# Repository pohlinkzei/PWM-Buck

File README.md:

# PWM-Buck
AVR-based control unit for car heating and ventilation in combination with an auxiliary heating

Its based on a Atmega88/168/328 AVR with a buck-converter power amplifier. It is made to driva a 
200W Motor for car heating and to display the water temperature, the temperature of the power 
transistors and the battery voltage. 

Here is where the development begun:
http://www.t4forum.de/wbb3/board19-technik-bereich/board120-umbauten-tuning/board8-tipps-und-tricks/165848-gemeinschaftsentwicklung-t4forums-pwm-modul/

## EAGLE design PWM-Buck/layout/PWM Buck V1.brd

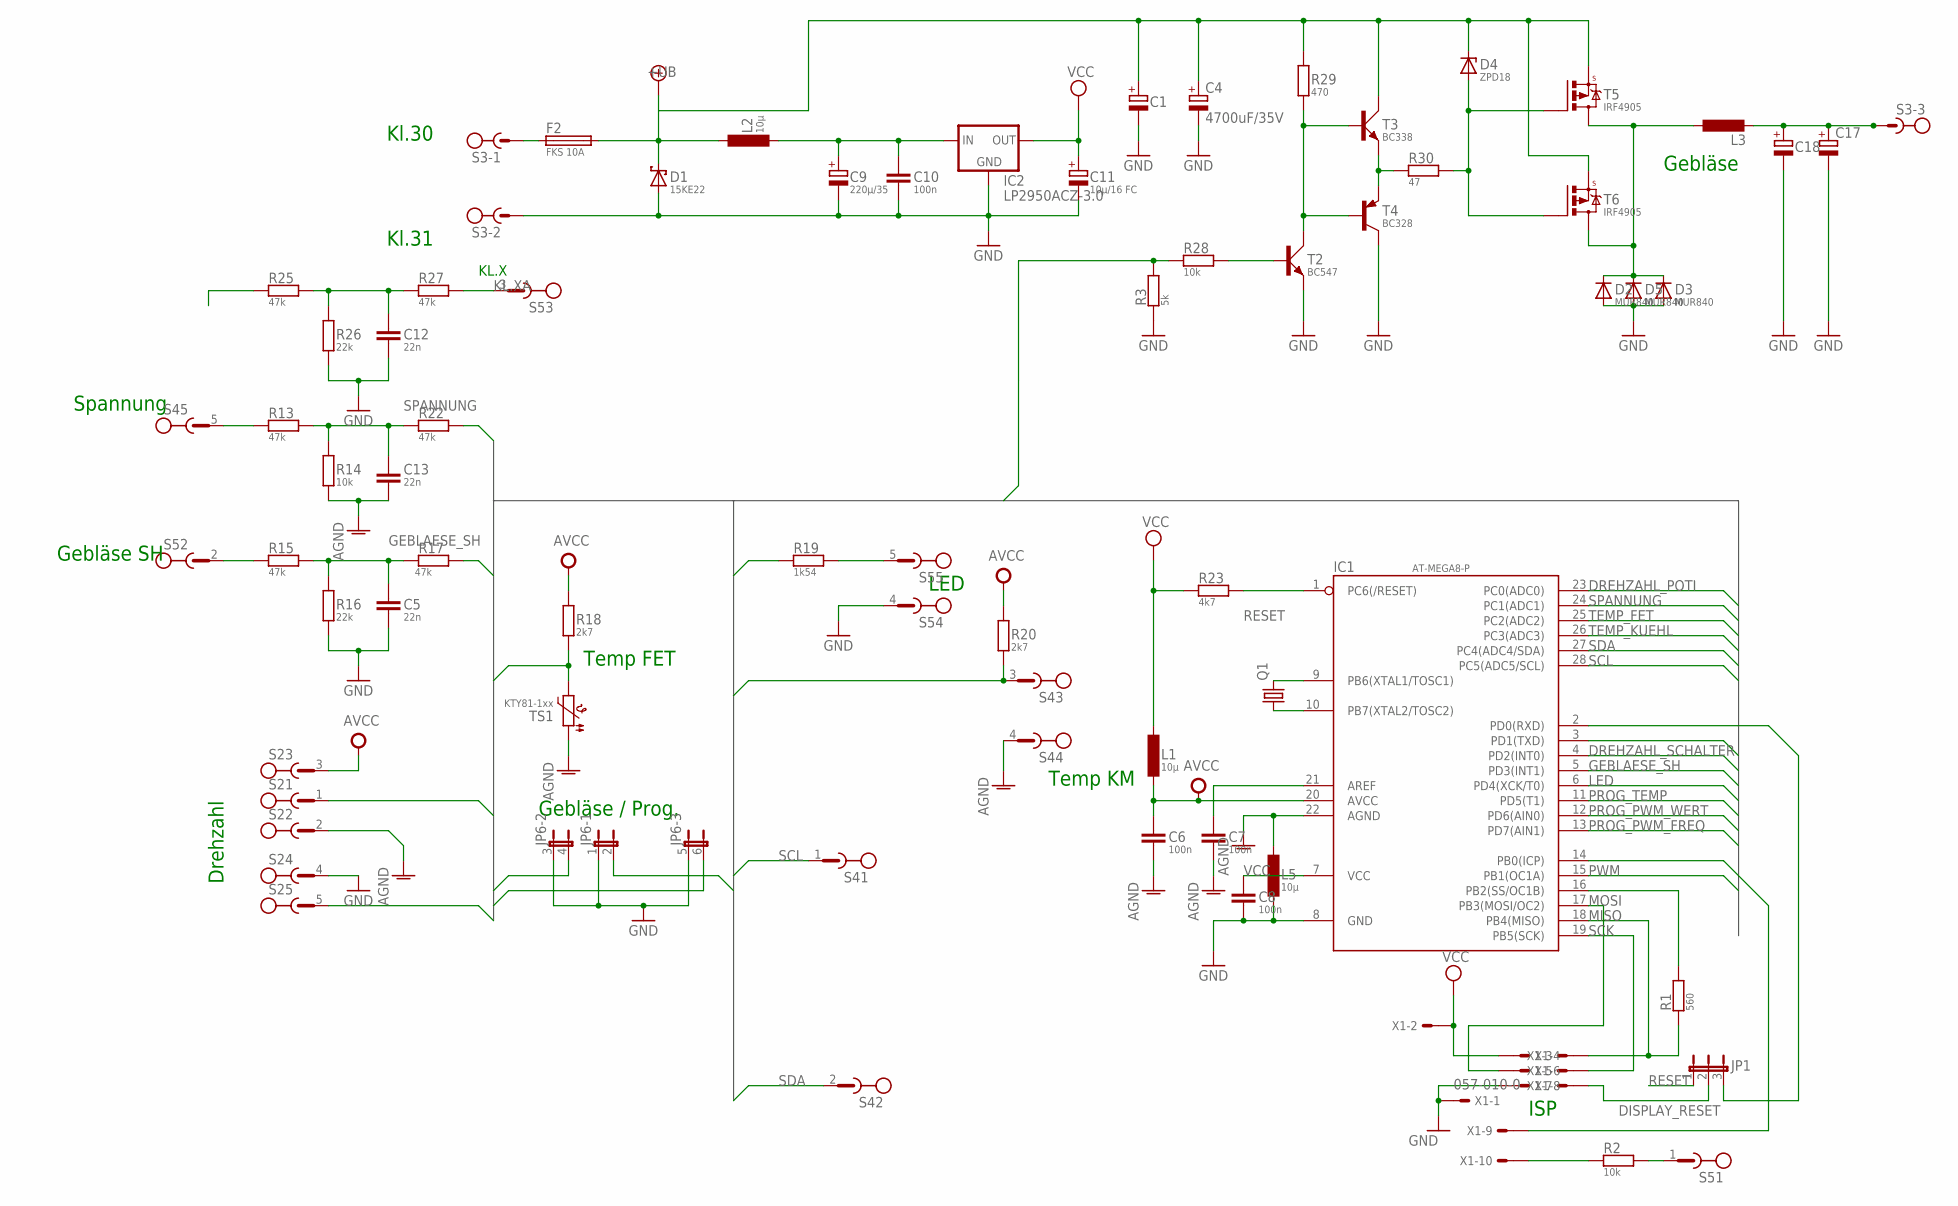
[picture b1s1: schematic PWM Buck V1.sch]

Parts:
C1, C18: C_POL_5-10.5; E5-10.5
C4: 4700uF/35V; E7,5-18
C5, C12, C13: 22n; C_75_SCHMAL
C6, C7, C8: 100n; C_50_SCHMAL
C9: 220µ/35; E5-10.5
C10: 100n; C_75_SCHMAL
C11: 10µ/16 FC; E2.5-5
C17: CPOL-EUE5-13; E5-13
D1: 15KE22; DO201T15
D2, D3, D5: MUR840; TO220ACS
D4: ZPD18; DO35Z10
F2: FKS 10A; FKS
IC1: AT-MEGA8-P; AT-MEGA8P
IC2: LP2950ACZ-3.0; TO92
JP1: JP2E; JP2
JP6: JP3QE; JP3Q
L1, L2, L5: 10µ; L-2200-12,7
L3: L-EU0207/12; 0207/12
Q1: CRYSTALTC26V; TC26V
R1: 560; R_10
R2, R14, R28: 10k; R_10
R3: 5k; R_10
R13, R15, R17, R22, R25, R27: 47k; R_10
R16, R26: 22k; R_10
R18: 2k7; R_10
R19: 1k54; R_10
R20: 2k7; R_12
R23: 4k7; R_10
R29: 470; R_10
R30: 47; R_10
S2: CON-PLATINE_5-POLIG
S3: CON-RIA-220-03; RIA-220-03
S4, S5: CON-RIA-183-05; RIA-183-05
T2: BC547; SOT54A-WIDE
T3: BC338; SOT54A-WIDE
T4: BC328; TO92_WIDE
T5, T6: IRF4905; TO220BV
TS1: KTY81-1xx; SOD70
X1: 057-010-0

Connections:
+UB: C1.+, C4.+, D1.C, D4.C, F2.2, L2.2, R29.2, T3.C, T5.S, T6.S
AGND: C6.2, C7.2, C13.1, IC1.22 (AGND), L5.2, R14.1, S2.2, S4.4, TS1.1
AVCC: C6.1, IC1.20 (AVCC), L1.1, R18.2, R20.2, S2.3
BEL_K58B: R2.2, X1.10
BEL_SH: IC1.14 (PB0(ICP)), X1.9
DISPLAY_RESET: JP1.2, X1.7
DREHZAHL_POTI: IC1.23 (PC0(ADC0)), S2.1
DREHZAHL_SCHALTER: IC1.4 (PD2(INT0)), S2.5
GATE: D4.A, R30.1, T5.G, T6.G
GEBLAESE_OUT: D2.C, D3.C, D5.C, L3.1, T5.D, T6.D
GEBLAESE_SH: IC1.5 (PD3(INT1)), R17.1
GND: C1.-, C4.-, C5.1, C8.2, C9.-, C10.2, C11.-, C12.1, C17.-, C18.-, D1.A, D2.A, D3.A, D5.A, IC1.8 (GND), IC2.2 (GND), JP6.1, JP6.3 (1), JP6.5 (1), L5.1, R3.2, R16.1, R26.1, S2.4, S3.2, S5.4, T2.E, T4.3 (C), X1.1, X1.8
KL.X: IC1.3 (PD1(TXD)), R25.1
KL.XA: R27.1, S5.3
LED: IC1.6 (PD4(XCK/T0)), R19.2
MISO: IC1.18 (PB4(MISO)), R1.1, X1.3
MOSI: IC1.17 (PB3(MOSI/OC2)), X1.6
unnamed: IC1.9 (PB6(XTAL1/TOSC1)), Q1.2
unnamed: IC1.10 (PB7(XTAL2/TOSC2)), Q1.1
unnamed: IC1.16 (PB2(SS/OC1B)), R1.2
unnamed: F2.1, S3.1
unnamed: IC1.2 (PD0(RXD)), JP1.3
unnamed: C5.2, R15.2, R16.2, R17.2
unnamed: C9.+, C10.1, IC2.3 (IN), L2.1
unnamed: R29.1, T2.C, T3.B, T4.2 (B)
unnamed: R2.1, S5.1
unnamed: C17.+, C18.+, L3.2, S3.3
unnamed: C7.1, IC1.21 (AREF)
unnamed: R28.1, T2.B
unnamed: R30.2, T3.E, T4.1 (E)
unnamed: C12.2, R25.2, R26.2, R27.2
unnamed: R19.1, S5.5
NIX: C13.2, R13.2, R14.2, R22.1
PROG_PWM_FREQ: IC1.13 (PD7(AIN1)), JP6.6 (2)
PROG_PWM_WERT: IC1.12 (PD6(AIN0)), JP6.4 (2)
PROG_TEMP: IC1.11 (PD5(T1)), JP6.2
PWM: IC1.15 (PB1(OC1A)), R3.1, R28.2
RESET: IC1.1 (PC6(/RESET)), JP1.1, R23.2
SCK: IC1.19 (PB5(SCK)), X1.5
SCL: IC1.28 (PC5(ADC5/SCL)), S4.1
SDA: IC1.27 (PC4(ADC4/SDA)), S4.2
SH: R15.1, S5.2
SPANNUNG: IC1.24 (PC1(ADC1)), R22.2
SPG: R13.1, S4.5
TEMP_FET: IC1.25 (PC2(ADC2)), R18.1, TS1.2
TEMP_KUEHL: IC1.26 (PC3(ADC3)), R20.1, S4.3
VCC: C8.1, C11.+, IC1.7 (VCC), IC2.1 (OUT), L1.2, R23.1, X1.2, X1.4

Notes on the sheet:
Drehzahl
Gebläse / Prog.
Temp FET
Temp KM
Kl.31
Kl.30
Spannung
LED
Gebläse SH
ISP
Gebläse
KL.X

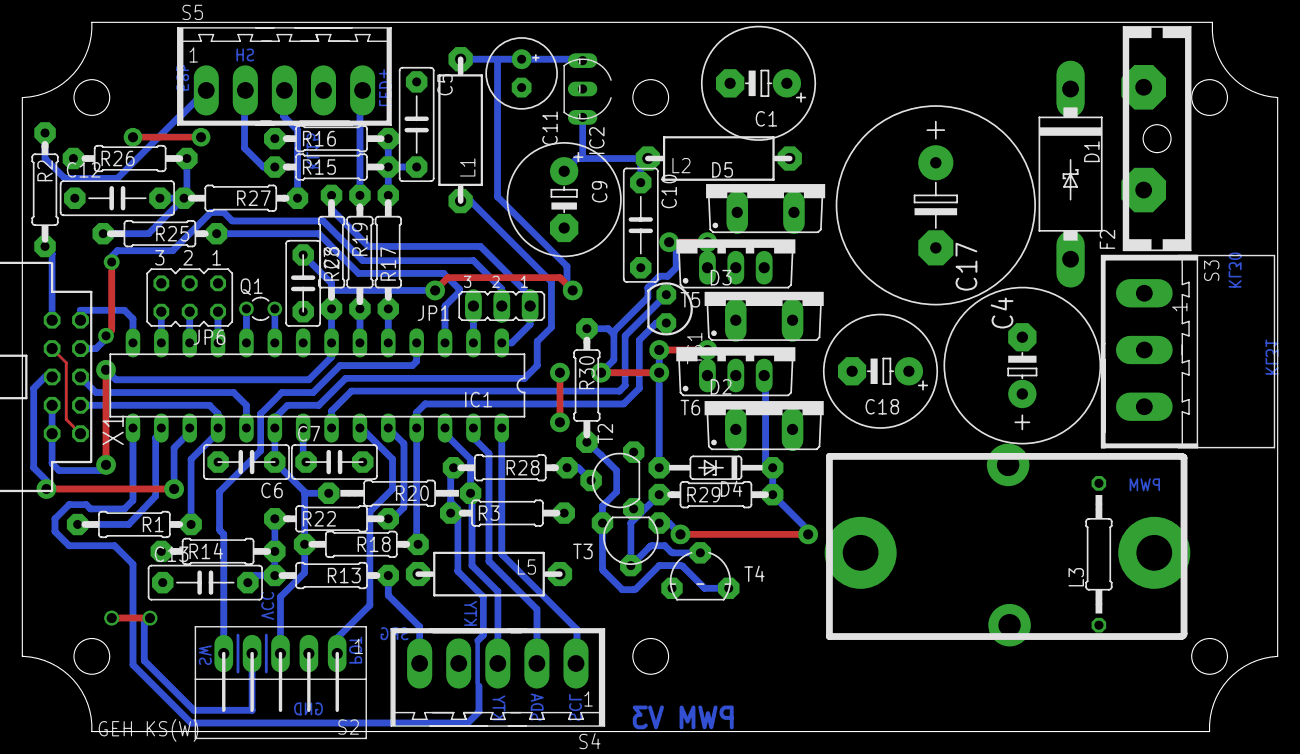
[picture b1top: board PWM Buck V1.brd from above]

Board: 2 copper layers, 112.4 x 63.5 mm, 59 parts (0 on the bottom side), 47 nets.

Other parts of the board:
U$1: GEH_KSW_120X170

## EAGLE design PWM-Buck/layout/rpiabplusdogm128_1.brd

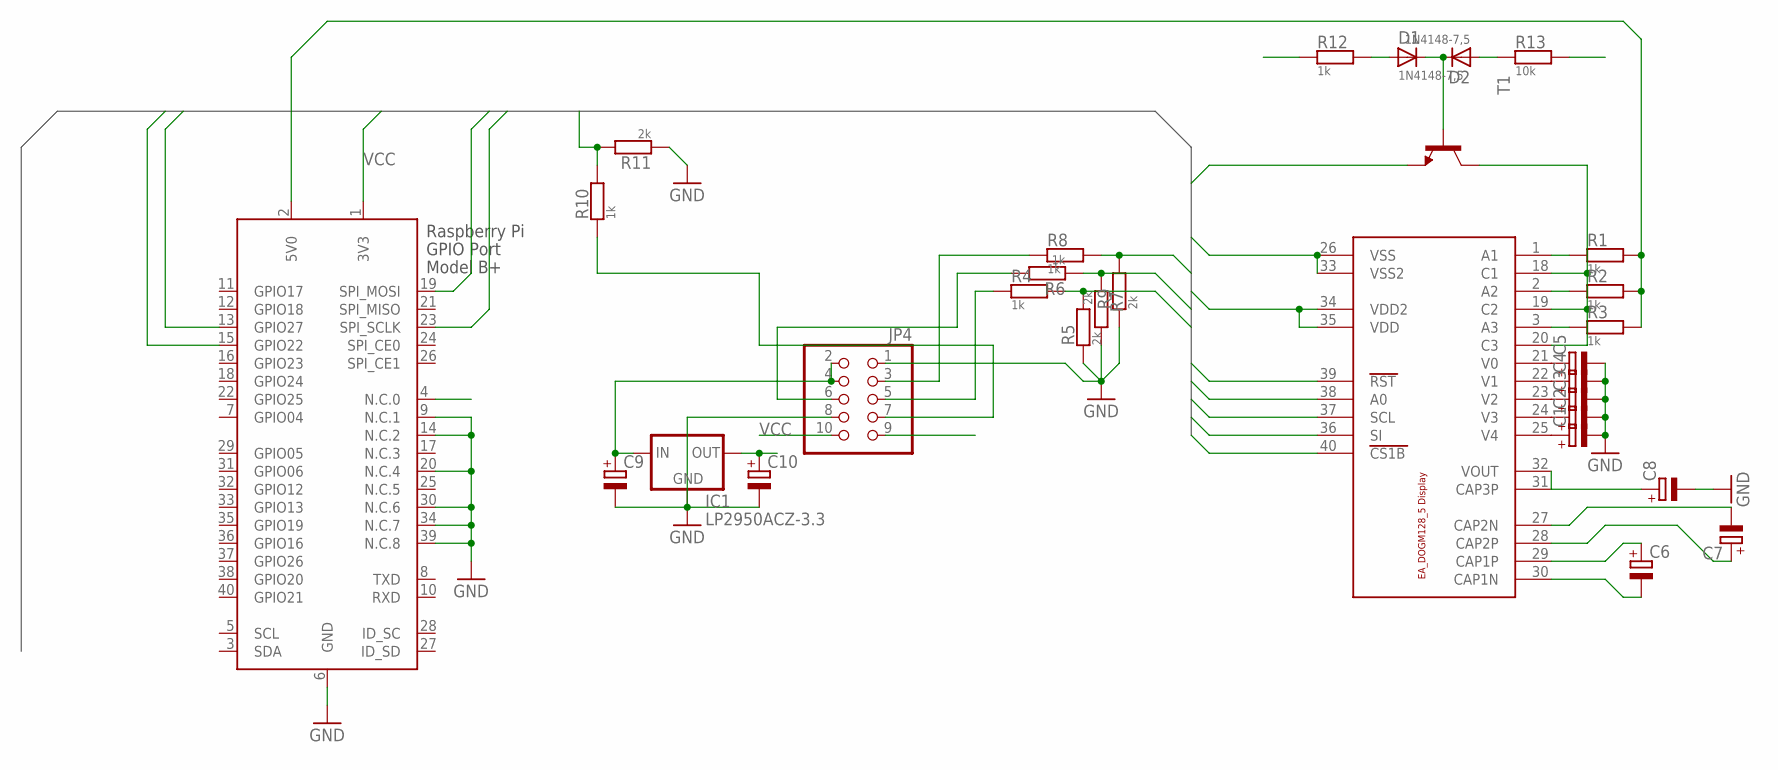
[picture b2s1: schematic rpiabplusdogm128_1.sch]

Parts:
C1, C2, C3, C4, C5, C6, C7, C8, C9, C10: CPOL-EUA/3216-18W; A/3216-18W
D1, D2: 1N4148-7,5; DO35-7,5
IC1: LP2950ACZ-3.3; TO92
JP4: PINHD-2X5_2.54-SMD; 2X05SMD
R1, R2, R3, R4, R6, R8, R10, R12: 1k; R_10
R5, R7, R9, R11: 2k; R_10
R13: 10k; R_10
T1: BC817-16-NPN-SOT23-BEC; SOT23-BEC
U$1: EA_DOG-M_DISPLAY; E_DOG-M_DISPLAY
X2: RASPI_BOARD_B+_H; RASPI_BOARD_B+HAT

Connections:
5V: C9.+, IC1.3 (IN), JP4.2, JP4.4, R1.2, R2.2, R3.2, X2.2 (5V0), X2.4 (N.C.0)
A0: R8.2, R9.2, U$1.38 (A0), X2.15 (GPIO22)
BELE: JP4.9, R12.1
BELK58B: JP4.10, R13.2
CS1B: U$1.40 (CS1B)
GND: C1.-, C2.-, C3.-, C4.-, C5.-, C8.-, C9.-, C10.-, IC1.2 (GND), JP4.1, JP4.8, R5.1, R7.2, R9.1, R11.1, T1.E, U$1.26 (VSS), U$1.33 (VSS2), X2.6 (GND), X2.9 (N.C.1), X2.14 (N.C.2), X2.20 (N.C.4), X2.30 (N.C.6), X2.34 (N.C.7), X2.39 (N.C.8)
unnamed: C1.+, U$1.25 (V4)
unnamed: R1.1, U$1.1 (A1)
unnamed: R2.1, U$1.2 (A2)
unnamed: R3.1, U$1.3 (A3)
unnamed: T1.C, U$1.18 (C1), U$1.19 (C2), U$1.20 (C3)
unnamed: JP4.7, R10.1
unnamed: JP4.5, R4.1
unnamed: JP4.6, R6.2
unnamed: JP4.3, R8.1
unnamed: D1.C, D2.C, T1.B
unnamed: D2.A, R13.1
unnamed: D1.A, R12.2
unnamed: C2.+, U$1.24 (V3)
unnamed: C3.+, U$1.23 (V2)
unnamed: C4.+, U$1.22 (V1)
unnamed: C5.+, U$1.21 (V0)
unnamed: C8.+, U$1.31 (CAP3P), U$1.32 (VOUT)
unnamed: C7.-, U$1.27 (CAP2N)
unnamed: C7.+, U$1.28 (CAP2P)
unnamed: C6.+, U$1.29 (CAP1P)
unnamed: C6.-, U$1.30 (CAP1N)
RST: R10.2, R11.2, U$1.39 (RST), X2.13 (GPIO27)
SCL: R4.2, R5.2, U$1.37 (SCL), X2.23 (SPI_SCLK)
SI: R6.1, R7.1, U$1.36 (SI), X2.19 (SPI_MOSI)
VCC: C10.+, IC1.1 (OUT), U$1.34 (VDD2), U$1.35 (VDD), X2.1 (3V3)

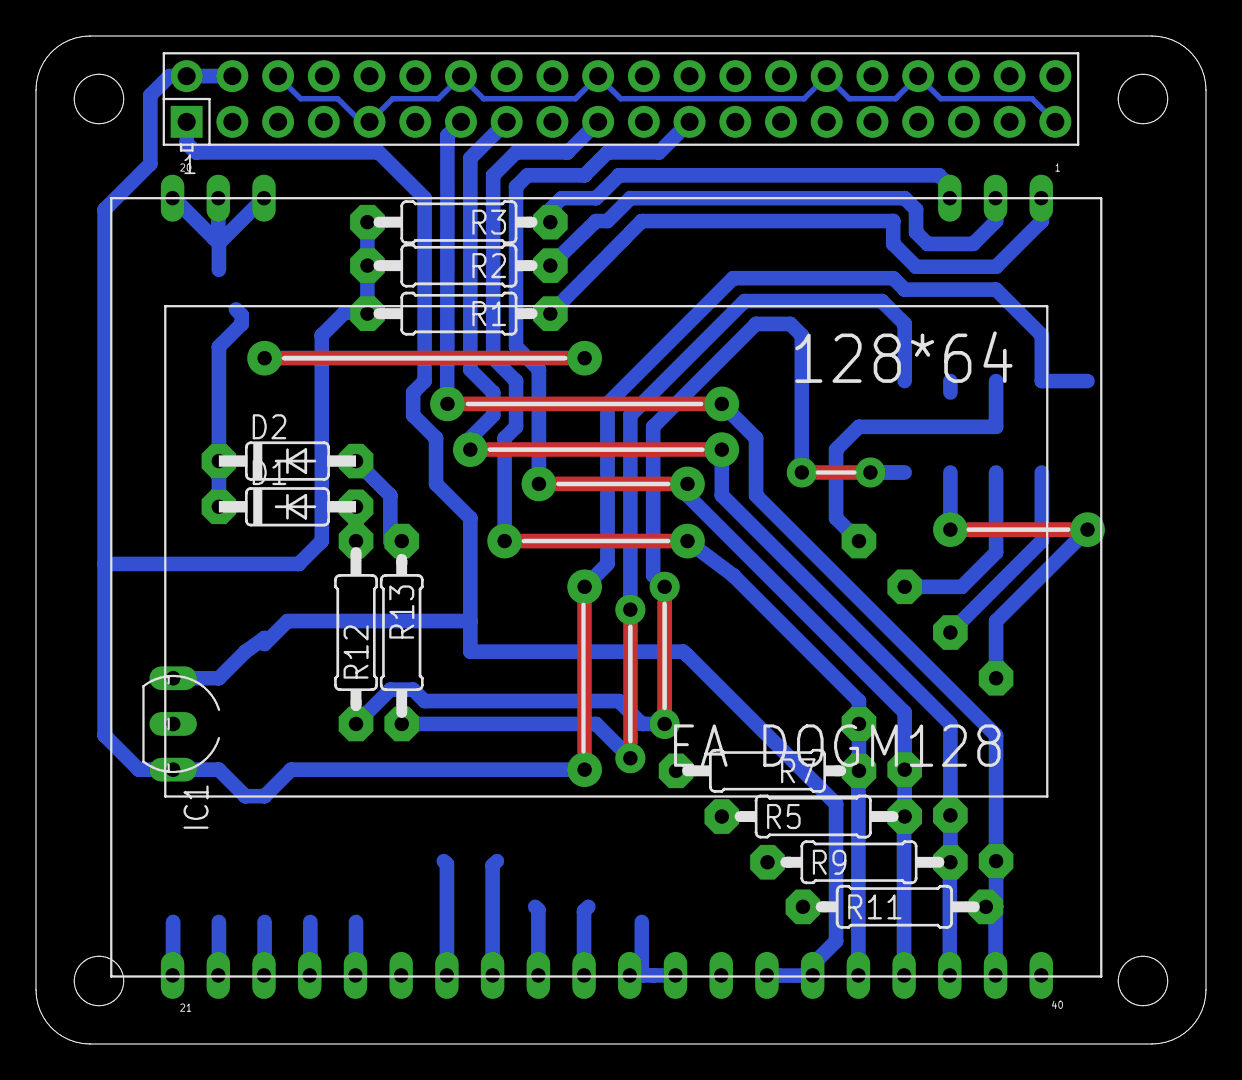
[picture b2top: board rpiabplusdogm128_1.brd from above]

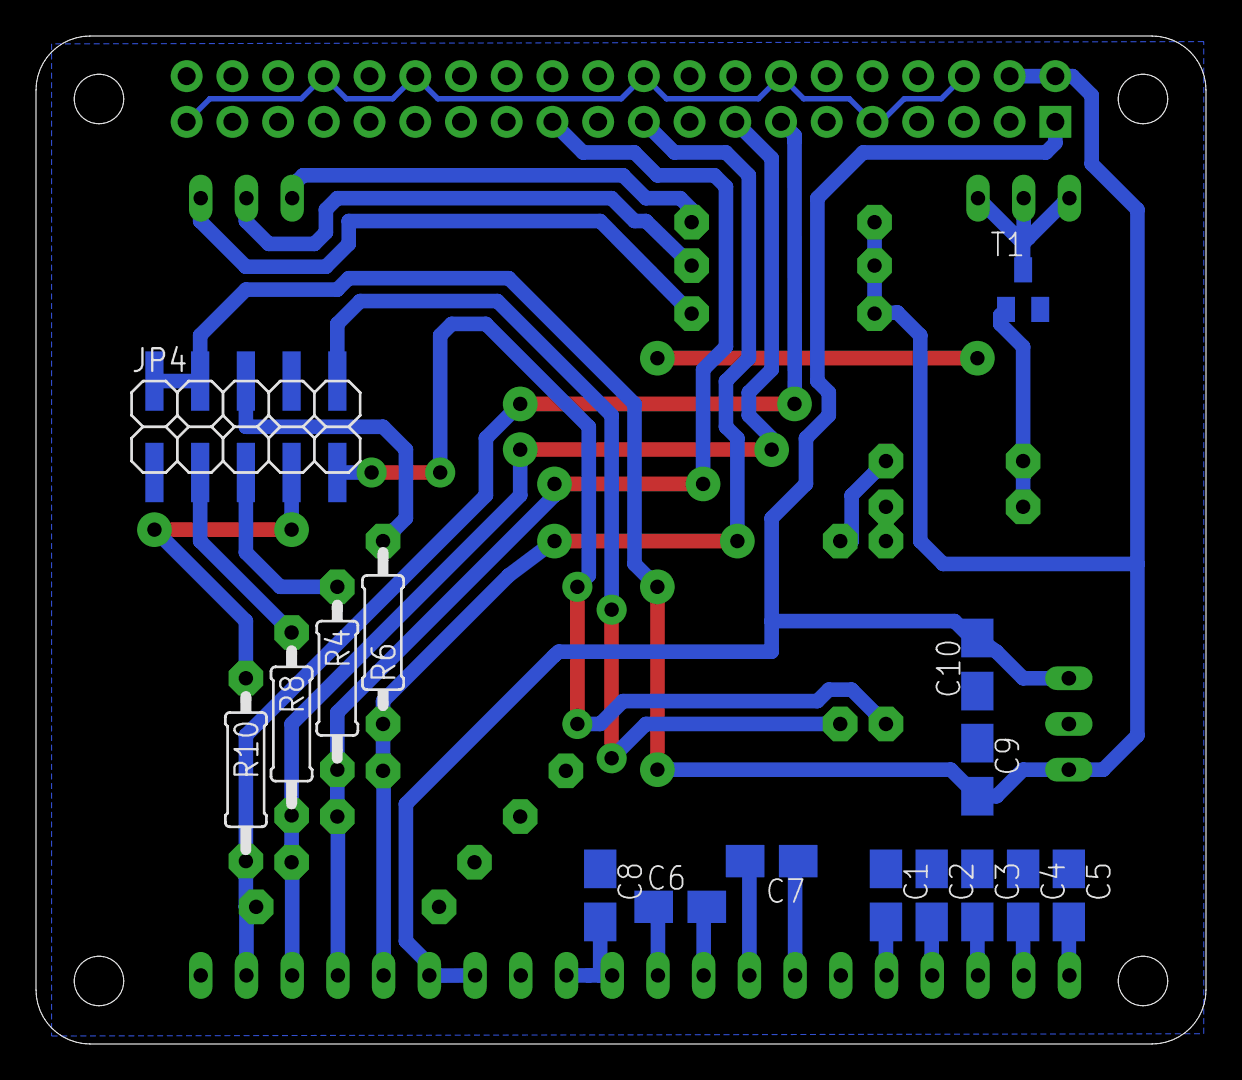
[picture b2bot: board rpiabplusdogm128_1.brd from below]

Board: 2 copper layers, 65.0 x 56.0 mm, 30 parts (16 on the bottom side), 30 nets.

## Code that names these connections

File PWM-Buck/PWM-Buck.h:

/*
 * PWM_V1.h
 *
 * T4Forum-PWM-Module
 *
 * Created: 03.03.2012 13:33:06
 *  Author: hubert (Robert)
 */ 

#ifndef PWM_BUCK_H
#define PWM_BUCK_H

#include <avr/io.h>
#include <stdbool.h>
//#include <stdlib.h>
#include <avr/eeprom.h>
//#include "dog_display."
#ifndef F_CPU
#define F_CPU 8000000
#endif


/* I/O descriptions */

//layout version: buck
#define DISPLAY_PORT PORTB
#define DISPLAY_DDR DDRB
#define DISPLAY_PIN PINB
#define DISPLAY_LIGHT PB0

#define SH_PORT PORTD
#define SH_DDR DDRD
#define SH_PIN PIND

#define IGNITION	PD1
#define POT_SWITCH	PD2
#define AUX_HEAT	PD3
//#define PROG_PWM_VALUE		PD6
#define PROG_PWM_FREQ		PD7
#define PROG_WATER_TEMP     PD5


#define POT_VALUE	PC0
#define BAT2VOLTAGE PC1
#define TEMP_WATER	PC3
#define TEMP_FET	PC2


#define LED			PD4
#define PWM			PB1

#define FILTER_VALUE 2 //must be between 0 and 6

#define SYM_BAT1 "\x01"
#define SYM_BAT2 "\x02"
#define SYM_FET "\x03"
#define SYM_TEMP "\x04"
#define SYM_WTEMP1 "\x05"
#define SYM_WTEMP2 "\x06"

#define MIN_PWM_FREQUENCY 20
#define MAX_PWM_FREQUENCY 32768

#define MAX_FET_TEMP 115

#define MIN_BAT_VOLTAGE 1120//set in centiVolts

typedef enum stat{
	OFF = 0,
	IGNITION_ON,
	AUX_HEAT_ON,
	PROGRAM,
	ERROR,
}status_t;

typedef struct vol_val{
	int8_t integer;
	uint8_t fraction;
}voltage_value_t;

bool compare_string(uint16_t *str1, uint16_t *str2, uint8_t length);
int16_t calculate_temperature(uint16_t adc);
uint16_t read_adc(uint8_t portbit);
uint8_t calculate_pwm_percent(void);
voltage_value_t calculate_voltage(uint16_t adc);
void transmit_value(uint8_t page, uint8_t code, uint16_t value);
void print_error(void);

#endif

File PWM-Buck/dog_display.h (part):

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#define COLUMNS 132
#define ROWS 8//4

#define DOG_A0 PB2
#define DOG_A0_DDR DDRB
#define DOG_A0_PORT PORTB
/*#define CS1B 0x00*/
#define DOG_RST PD0
#define DOG_RST_DDR DDRD
#define DOG_RST_PORT PORTD

#define SPI_DDR DDRB
#define MOSI PB3
#define MISO PB4
#define SCK PB5

//dog COMMANDS
#define LCD_ON			0xAF
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
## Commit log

2015-08-27 Fix: Typo
2015-08-27 Add: Layout
2015-08-27 fix: Symbols for FET temperature and water temperature
2015-08-27 FIX: link
2015-08-31 update: almost ready
2015-09-14 update&fix
2015-09-21 some minor fixes
2015-09-23 Add working i2c interface
2015-09-23 update twi-interface
2015-12-16 update: switch off pwm output for power down
2015-12-17 update: twi and power off pwm
2016-01-31 Fix twi part
2016-02-03 Fix twi - tested and working now...
2016-06-30 minor changes
